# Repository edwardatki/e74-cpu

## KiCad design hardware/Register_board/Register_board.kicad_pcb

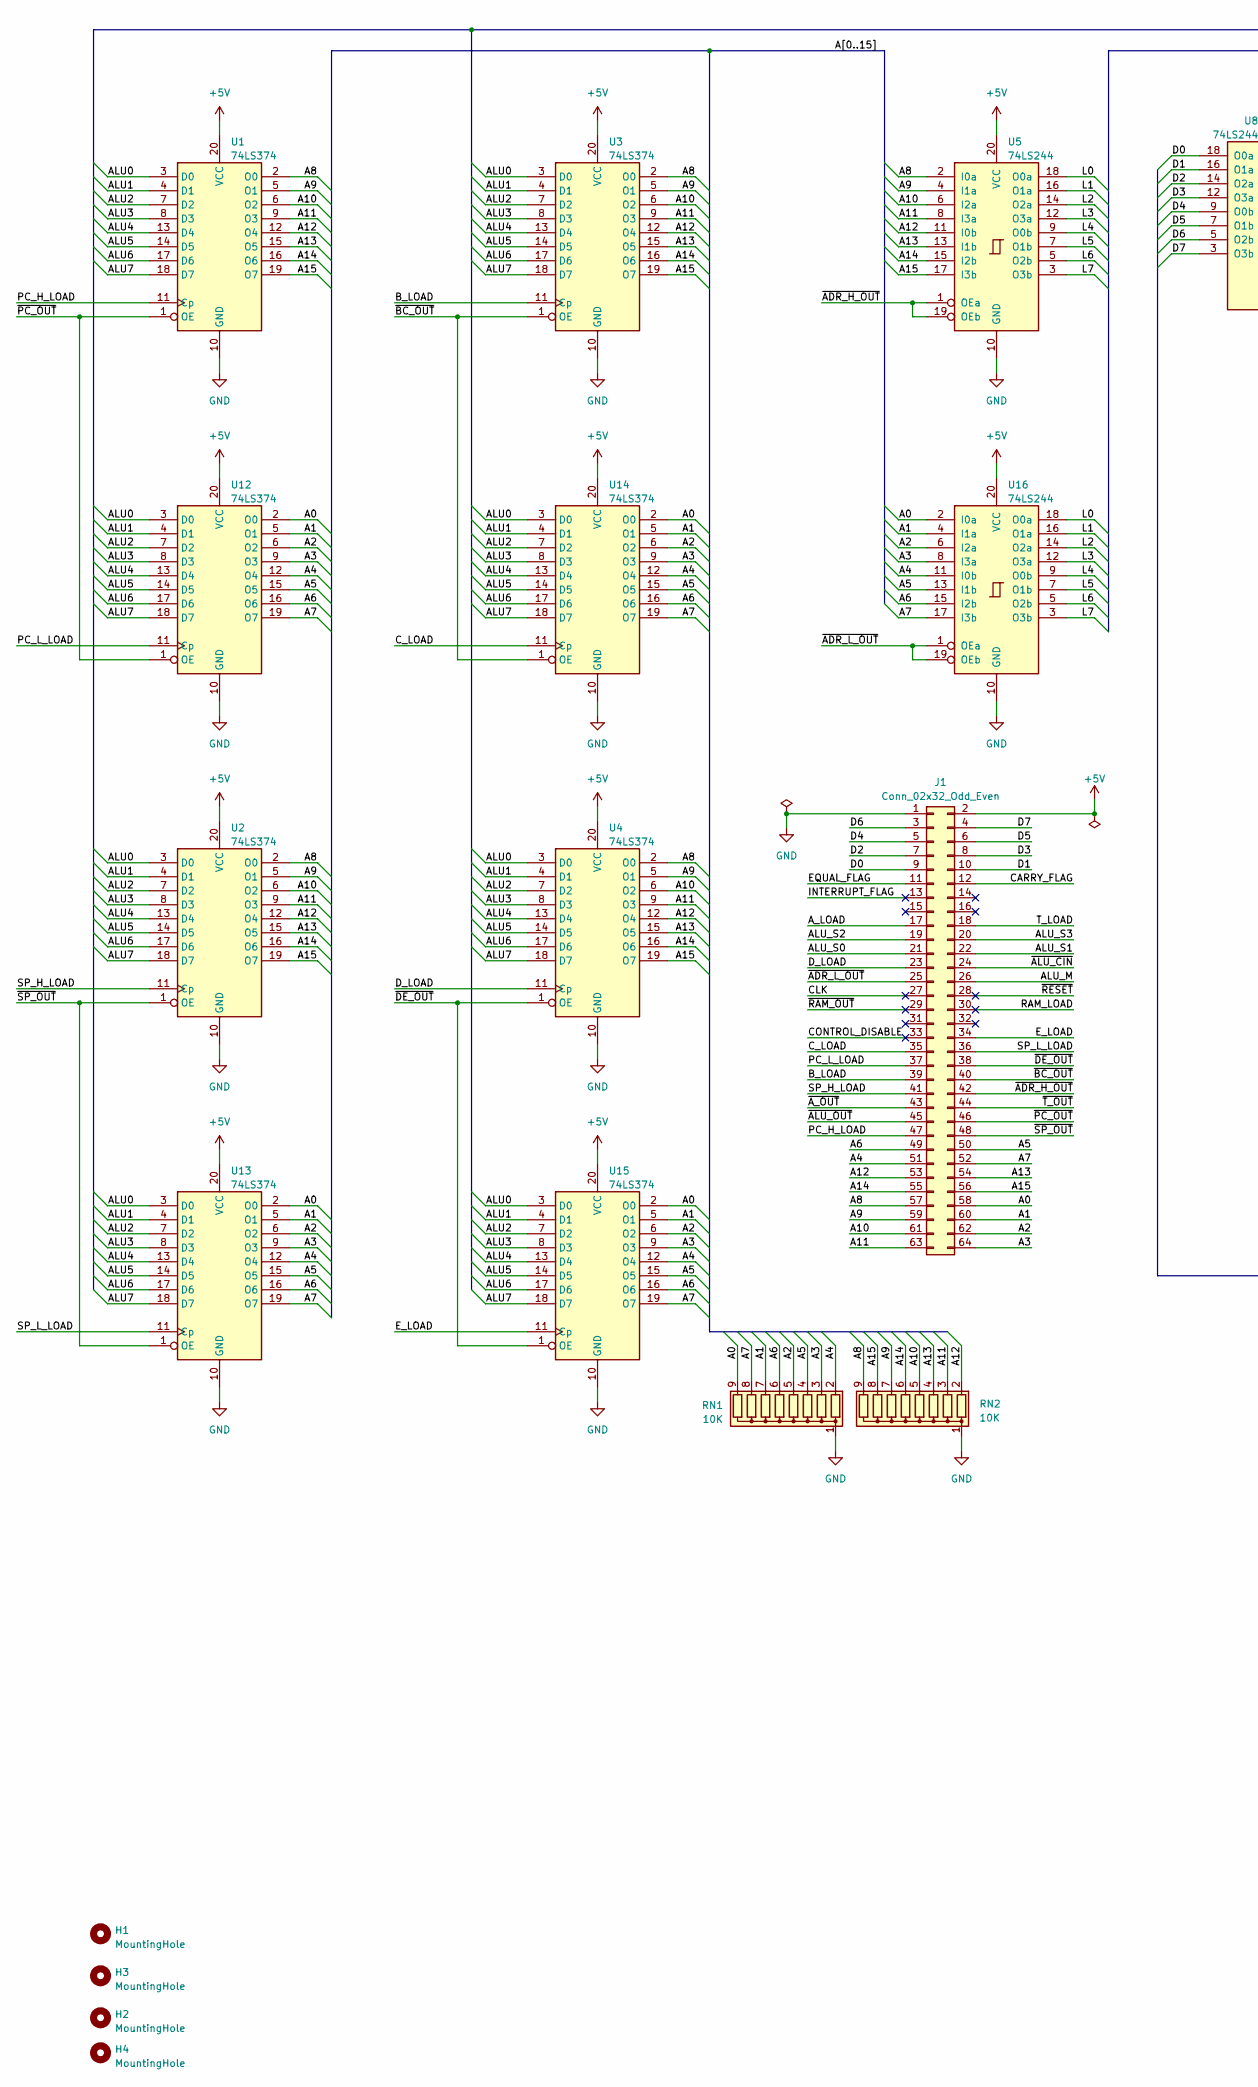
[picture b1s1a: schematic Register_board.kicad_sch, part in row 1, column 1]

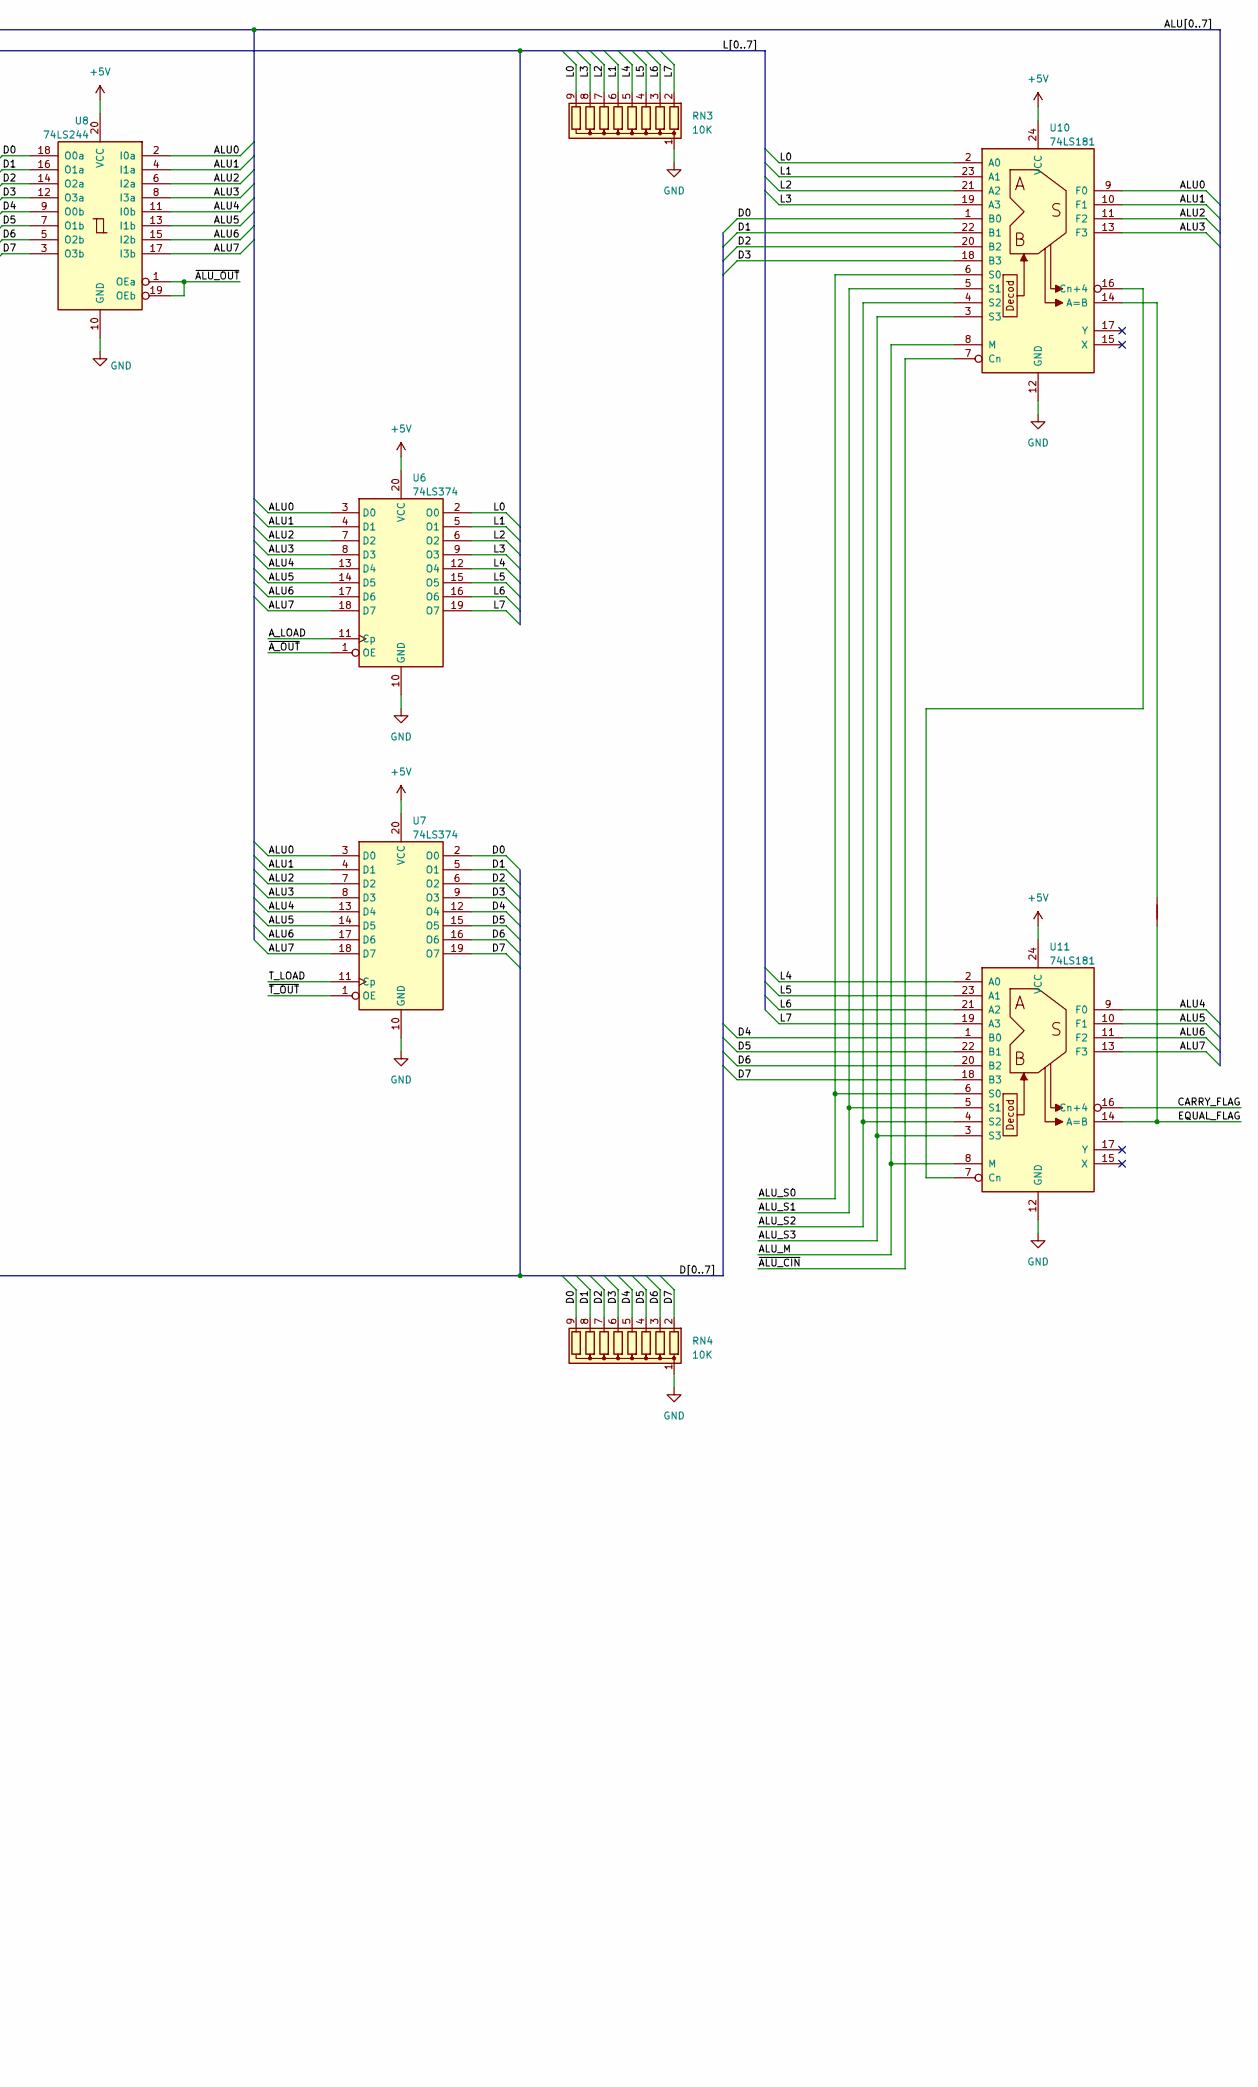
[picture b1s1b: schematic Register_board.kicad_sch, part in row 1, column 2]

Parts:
H1, H2, H3, H4: MountingHole; MountingHole_3.5mm
J1: Conn_02x32_Odd_Even; IDC-Header_2x32_P2.54mm_Vertical
NT1: NetTie_2; NetTie-2_SMD_Pad0.5mm
RN1, RN2, RN3, RN4: 10K; R_Array_SIP9
U1, U2, U3, U4, U6, U7, U12, U13, U14, U15: 74LS374; DIP-20_W7.62mm_Socket
U5, U8, U16: 74LS244; DIP-20_W7.62mm_Socket
U10, U11: 74LS181; DIP-24_W15.24mm_Socket

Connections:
+5V: J1.2, U1.20 (VCC), U2.20 (VCC), U3.20 (VCC), U4.20 (VCC), U5.20 (VCC), U6.20 (VCC), U7.20 (VCC), U8.20 (VCC), U10.24 (VCC), U11.24 (VCC), U12.20 (VCC), U13.20 (VCC), U14.20 (VCC), U15.20 (VCC), U16.20 (VCC); also elsewhere on the board
/A0: J1.58, RN1.9 (R8), U12.2 (O0), U13.2 (O0), U14.2 (O0), U15.2 (O0), U16.2 (I0a)
/A1: J1.60, RN1.7 (R6), U12.5 (O1), U13.5 (O1), U14.5 (O1), U15.5 (O1), U16.4 (I1a)
/A2: J1.62, RN1.5 (R4), U12.6 (O2), U13.6 (O2), U14.6 (O2), U15.6 (O2), U16.6 (I2a)
/A3: J1.64, RN1.3 (R2), U12.9 (O3), U13.9 (O3), U14.9 (O3), U15.9 (O3), U16.8 (I3a)
/A4: J1.51, RN1.2 (R1), U12.12 (O4), U13.12 (O4), U14.12 (O4), U15.12 (O4), U16.11 (I0b)
/A5: J1.50, RN1.4 (R3), U12.15 (O5), U13.15 (O5), U14.15 (O5), U15.15 (O5), U16.13 (I1b)
/A6: J1.49, RN1.6 (R5), U12.16 (O6), U13.16 (O6), U14.16 (O6), U15.16 (O6), U16.15 (I2b)
/A7: J1.52, RN1.8 (R7), U12.19 (O7), U13.19 (O7), U14.19 (O7), U15.19 (O7), U16.17 (I3b)
/A8: J1.57, RN2.9 (R8), U1.2 (O0), U2.2 (O0), U3.2 (O0), U4.2 (O0), U5.2 (I0a)
/A9: J1.59, RN2.7 (R6), U1.5 (O1), U2.5 (O1), U3.5 (O1), U4.5 (O1), U5.4 (I1a)
/A10: J1.61, RN2.5 (R4), U1.6 (O2), U2.6 (O2), U3.6 (O2), U4.6 (O2), U5.6 (I2a)
/A11: J1.63, RN2.3 (R2), U1.9 (O3), U2.9 (O3), U3.9 (O3), U4.9 (O3), U5.8 (I3a)
/A12: J1.53, RN2.2 (R1), U1.12 (O4), U2.12 (O4), U3.12 (O4), U4.12 (O4), U5.11 (I0b)
/A13: J1.54, RN2.4 (R3), U1.15 (O5), U2.15 (O5), U3.15 (O5), U4.15 (O5), U5.13 (I1b)
/A14: J1.55, RN2.6 (R5), U1.16 (O6), U2.16 (O6), U3.16 (O6), U4.16 (O6), U5.15 (I2b)
/A15: J1.56, RN2.8 (R7), U1.19 (O7), U2.19 (O7), U3.19 (O7), U4.19 (O7), U5.17 (I3b)
/ALU0: U1.3 (D0), U2.3 (D0), U3.3 (D0), U4.3 (D0), U6.3 (D0), U7.3 (D0), U8.2 (I0a), U10.9 (F0), U12.3 (D0), U13.3 (D0), U14.3 (D0), U15.3 (D0)
/ALU1: U1.4 (D1), U2.4 (D1), U3.4 (D1), U4.4 (D1), U6.4 (D1), U7.4 (D1), U8.4 (I1a), U10.10 (F1), U12.4 (D1), U13.4 (D1), U14.4 (D1), U15.4 (D1)
/ALU2: U1.7 (D2), U2.7 (D2), U3.7 (D2), U4.7 (D2), U6.7 (D2), U7.7 (D2), U8.6 (I2a), U10.11 (F2), U12.7 (D2), U13.7 (D2), U14.7 (D2), U15.7 (D2)
/ALU3: U1.8 (D3), U2.8 (D3), U3.8 (D3), U4.8 (D3), U6.8 (D3), U7.8 (D3), U8.8 (I3a), U10.13 (F3), U12.8 (D3), U13.8 (D3), U14.8 (D3), U15.8 (D3)
/ALU4: U1.13 (D4), U2.13 (D4), U3.13 (D4), U4.13 (D4), U6.13 (D4), U7.13 (D4), U8.11 (I0b), U11.9 (F0), U12.13 (D4), U13.13 (D4), U14.13 (D4), U15.13 (D4)
/ALU5: U1.14 (D5), U2.14 (D5), U3.14 (D5), U4.14 (D5), U6.14 (D5), U7.14 (D5), U8.13 (I1b), U11.10 (F1), U12.14 (D5), U13.14 (D5), U14.14 (D5), U15.14 (D5)
/ALU6: U1.17 (D6), U2.17 (D6), U3.17 (D6), U4.17 (D6), U6.17 (D6), U7.17 (D6), U8.15 (I2b), U11.11 (F2), U12.17 (D6), U13.17 (D6), U14.17 (D6), U15.17 (D6)
/ALU7: U1.18 (D7), U2.18 (D7), U3.18 (D7), U4.18 (D7), U6.18 (D7), U7.18 (D7), U8.17 (I3b), U11.13 (F3), U12.18 (D7), U13.18 (D7), U14.18 (D7), U15.18 (D7)
/ALU_M: J1.26, U10.8 (M), U11.8 (M)
/ALU_S0: J1.21, U10.6 (S0), U11.6 (S0)
/ALU_S1: J1.22, U10.5 (S1), U11.5 (S1)
/ALU_S2: J1.19, U10.4 (S2), U11.4 (S2)
/ALU_S3: J1.20, U10.3 (S3), U11.3 (S3)
/A_LOAD: J1.17, U6.11 (Cp)
/B_LOAD: J1.39, U3.11 (Cp)
/CARRY_FLAG_B: J1.16; also elsewhere on the board
/CLK: J1.27
/CONTROL_DISABLE: J1.33
/C_LOAD: J1.35, U14.11 (Cp)
/D0: J1.9, RN4.9 (R8), U7.2 (O0), U8.18 (O0a), U10.1 (B0)
/D1: J1.10, RN4.8 (R7), U7.5 (O1), U8.16 (O1a), U10.22 (B1)
/D2: J1.7, RN4.7 (R6), U7.6 (O2), U8.14 (O2a), U10.20 (B2)
/D3: J1.8, RN4.6 (R5), U7.9 (O3), U8.12 (O3a), U10.18 (B3)
/D4: J1.5, RN4.5 (R4), U7.12 (O4), U8.9 (O0b), U11.1 (B0)
/D5: J1.6, RN4.4 (R3), U7.15 (O5), U8.7 (O1b), U11.22 (B1)
/D6: J1.3, RN4.3 (R2), U7.16 (O6), U8.5 (O2b), U11.20 (B2)
/D7: J1.4, RN4.2 (R1), U7.19 (O7), U8.3 (O3b), U11.18 (B3)
/D_LOAD: J1.23, U4.11 (Cp)
/EQUAL_FLAG_B: J1.15; also elsewhere on the board
/E_LOAD: J1.34, U15.11 (Cp)
/FLAGS_A_UPDATE: J1.14; also elsewhere on the board
/FLAGS_B_UPDATE: J1.13; also elsewhere on the board
/L0: RN3.9 (R8), U5.18 (O0a), U6.2 (O0), U10.2 (A0), U16.18 (O0a)
/L1: RN3.6 (R5), U5.16 (O1a), U6.5 (O1), U10.23 (A1), U16.16 (O1a)
/L2: RN3.7 (R6), U5.14 (O2a), U6.6 (O2), U10.21 (A2), U16.14 (O2a)
/L3: RN3.8 (R7), U5.12 (O3a), U6.9 (O3), U10.19 (A3), U16.12 (O3a)
/L4: RN3.5 (R4), U5.9 (O0b), U6.12 (O4), U11.2 (A0), U16.9 (O0b)
/L5: RN3.4 (R3), U5.7 (O1b), U6.15 (O5), U11.23 (A1), U16.7 (O1b)
/L6: RN3.3 (R2), U5.5 (O2b), U6.16 (O6), U11.21 (A2), U16.5 (O2b)
/L7: RN3.2 (R1), U5.3 (O3b), U6.19 (O7), U11.19 (A3), U16.3 (O3b)
/PC_H_LOAD: J1.47, U1.11 (Cp)
/PC_L_LOAD: J1.37, U12.11 (Cp)
/RAM_LOAD: J1.30
/SP_H_LOAD: J1.41, U2.11 (Cp)
/SP_L_LOAD: J1.36, U13.11 (Cp)
/T_LOAD: J1.18, U7.11 (Cp)
/~ADR_H_OUT: J1.42, U5.1 (OEa), U5.19 (OEb)
/~ADR_L_OUT: J1.25, U16.1 (OEa), U16.19 (OEb)
/~ALU_CIN: J1.24, U10.7 (Cn)
/~ALU_OUT: J1.45, U8.1 (OEa), U8.19 (OEb)
/~A_OUT: J1.43, U6.1 (OE)
/~BC_OUT: J1.40, U3.1 (OE), U14.1 (OE)
/~DE_OUT: J1.38, U4.1 (OE), U15.1 (OE)
/~PC_OUT: J1.46, U1.1 (OE), U12.1 (OE)
/~RAM_OUT: J1.29
/~RESET: J1.28
/~SP_OUT: J1.48, U2.1 (OE), U13.1 (OE)
/~T_OUT: J1.44, U7.1 (OE)
GND: J1.1, RN1.1 (common), RN2.1 (common), RN3.1 (common), RN4.1 (common), U1.10 (GND), U2.10 (GND), U3.10 (GND), U4.10 (GND), U5.10 (GND), U6.10 (GND), U7.10 (GND), U8.10 (GND), U10.12 (GND), U11.12 (GND), U12.10 (GND), U13.10 (GND), U14.10 (GND), U15.10 (GND), U16.10 (GND); also elsewhere on the board
unnamed: NT1.1, U10.14 (A=B)
unnamed: U10.16 (Cn+4), U11.7 (Cn)

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
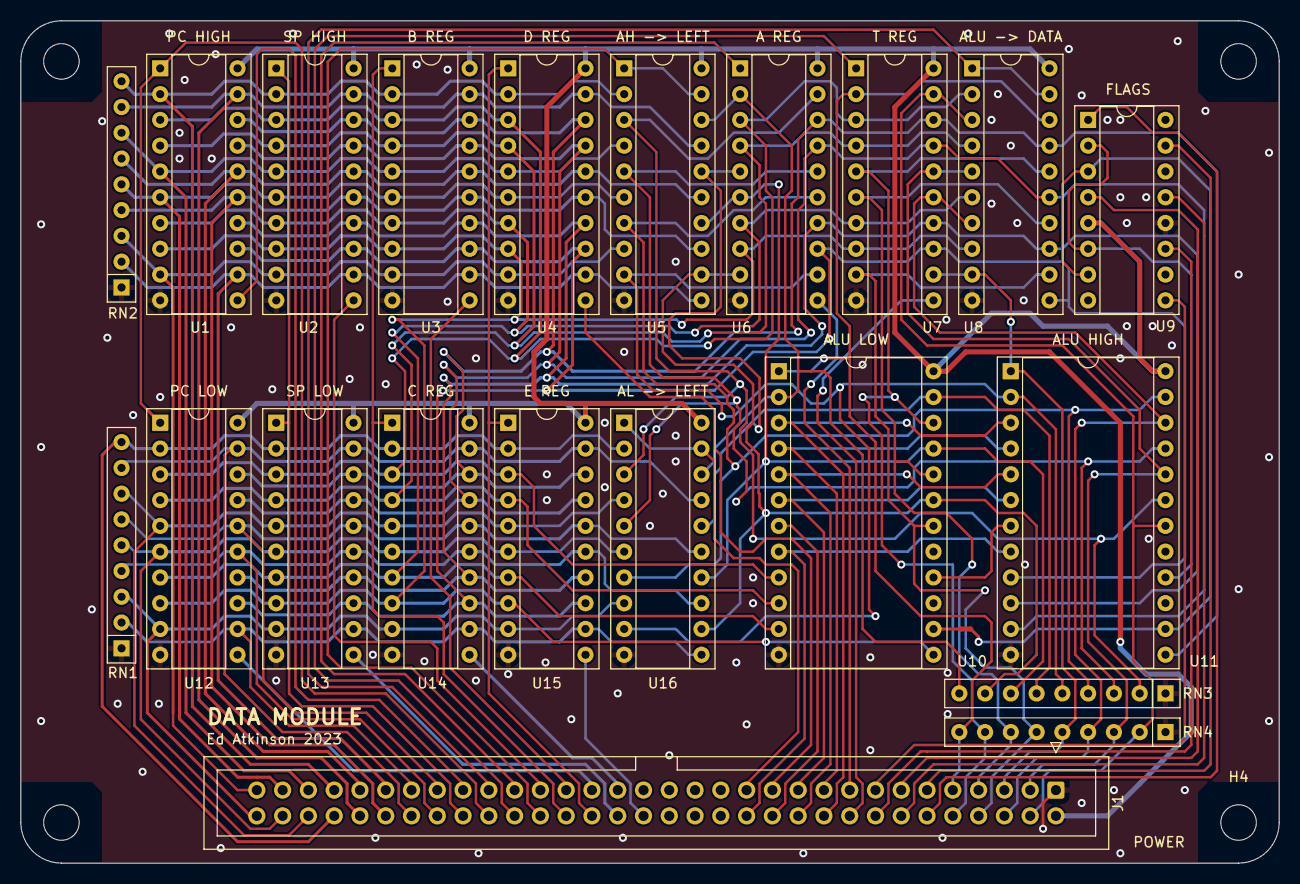
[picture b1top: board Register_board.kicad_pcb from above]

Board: 2 copper layers, 124.0 x 83.0 mm, 26 parts (0 on the bottom side), 77 nets.

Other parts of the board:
U9: 74LS75; DIP-16_W7.62mm_Socket

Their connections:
+5V: U9.5 (VCC); also elsewhere on the board
/CARRY_FLAG_B: U9.11 (~Q2); also elsewhere on the board
/EQUAL_FLAG_B: U9.9 (Q3); also elsewhere on the board
/FLAGS_A_UPDATE: U9.13 (E01); also elsewhere on the board
/FLAGS_B_UPDATE: U9.4 (E23); also elsewhere on the board
GND: U9.12 (GND); also elsewhere on the board

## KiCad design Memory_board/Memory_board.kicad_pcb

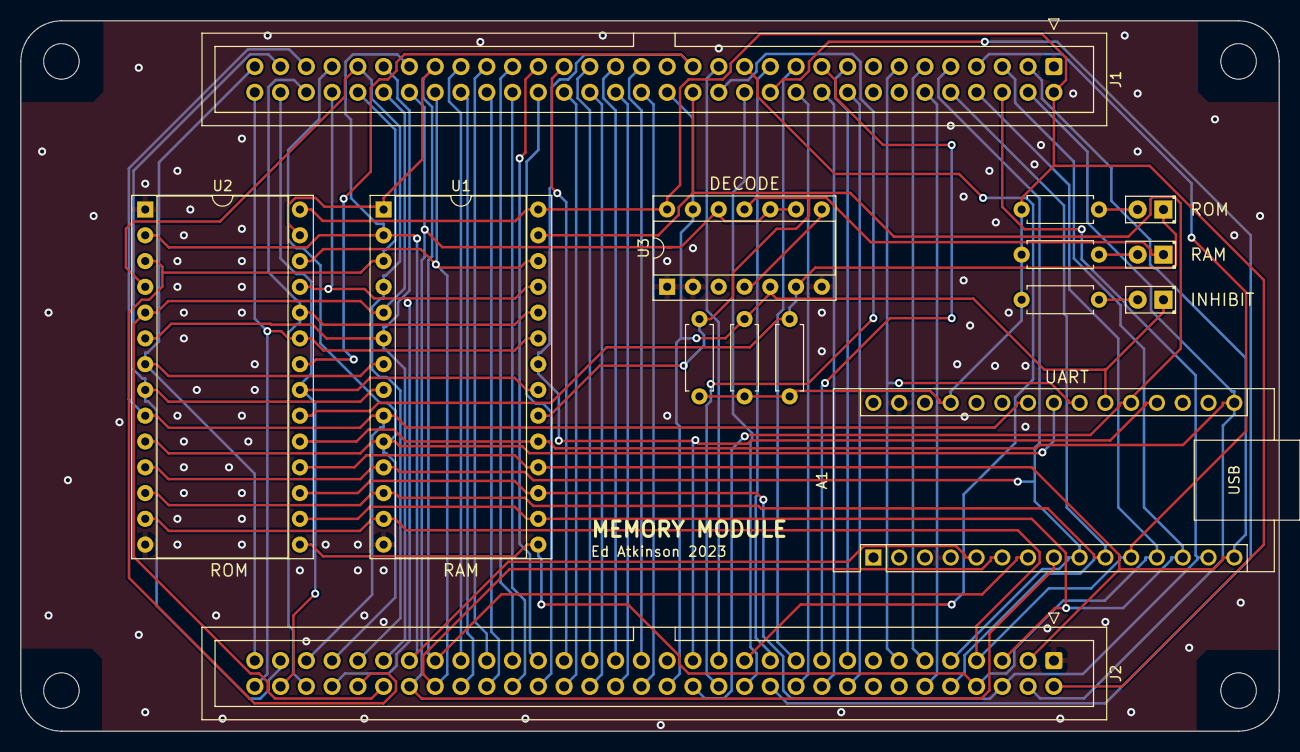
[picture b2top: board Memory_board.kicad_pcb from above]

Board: 2 copper layers, 124.0 x 70.0 mm, 19 parts (0 on the bottom side), 66 nets.

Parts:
A1: Arduino_Nano_v3.x; Arduino_Nano
D1, D2, D3: LED; LED_D2.0mm_W4.8mm_H2.5mm_FlatTop
H1, H2, H3, H4: MountingHole; MountingHole_3.5mm
J1, J2: Conn_02x32_Odd_Even; IDC-Header_2x32_P2.54mm_Vertical
R1, R5, R6: 1K; R_Axial_DIN0207_L6.3mm_D2.5mm_P7.62mm_Horizontal
R2, R3, R4: 330R; R_Axial_DIN0207_L6.3mm_D2.5mm_P7.62mm_Horizontal
U1: CY62256-70PC; DIP-28_W15.24mm_Socket
U2: 27C512; DIP-28_W15.24mm_Socket
U3: 74LS00; DIP-14_W7.62mm_Socket

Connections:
+5V: A1.27 (+5V), J1.2, J2.2, R1.2, R2.2, R3.2, R4.2, R5.1, R6.1, U1.28 (VCC), U2.28 (VCC), U3.14 (VCC)
/A0: A1.23 (A4), J1.57, J2.57, U1.10 (A0), U2.10 (A0)
/A1: A1.24 (A5), J1.59, J2.59, U1.9 (A1), U2.9 (A1)
/A2: J1.61, J2.61, U1.8 (A2), U2.8 (A2)
/A3: J1.63, J2.63, U1.7 (A3), U2.7 (A3)
/A4: J1.53, J2.53, U1.6 (A4), U2.6 (A4)
/A5: J1.54, J2.54, U1.5 (A5), U2.5 (A5)
/A6: J1.55, J2.55, U1.4 (A6), U2.4 (A6)
/A7: J1.56, J2.56, U1.3 (A7), U2.3 (A7)
/A8: J1.58, J2.58, U1.25 (A8), U2.25 (A8)
/A9: J1.60, J2.60, U1.24 (A9), U2.24 (A9)
/A10: J1.62, J2.62, U1.21 (A10), U2.21 (A10)
/A11: J1.64, J2.64, U1.23 (A11), U2.23 (A11)
/A12: A1.5 (D2), J1.51, J2.51, U1.2 (A12), U2.2 (A12)
/A13: A1.6 (D3), J1.50, J2.50, U1.26 (A13), U2.26 (A13)
/A14: A1.7 (D4), J1.49, J2.49, U1.1 (A14), U2.27 (A14)
/A15: A1.8 (D5), J1.52, J2.52, U3.9, U3.10, U3.12
/ALU_M: J1.26, J2.26
/ALU_S0: J1.21, J2.21
/ALU_S1: J1.22, J2.22
/ALU_S2: J1.19, J2.19
/ALU_S3: J1.20, J2.20
/A_LOAD: J1.17, J2.17
/B_LOAD: J1.39, J2.39
/CARRY_FLAG: J1.12, J2.12
/CLK: J1.27, J2.27
/CONTROL_DISABLE: J1.33, J2.33
/C_LOAD: J1.35, J2.35
/D0: A1.9 (D6), J1.9, J2.9, U1.11 (Q0), U2.11 (D0)
/D1: A1.10 (D7), J1.10, J2.10, U1.12 (Q1), U2.12 (D1)
/D2: A1.11 (D8), J1.7, J2.7, U1.13 (Q2), U2.13 (D2)
/D3: A1.12 (D9), J1.8, J2.8, U1.15 (Q3), U2.15 (D3)
/D4: A1.13 (D10), J1.5, J2.5, U1.16 (Q4), U2.16 (D4)
/D5: A1.14 (D11), J1.6, J2.6, U1.17 (Q5), U2.17 (D5)
/D6: A1.15 (D12), J1.3, J2.3, U1.18 (Q6), U2.18 (D6)
/D7: A1.16 (D13), J1.4, J2.4, U1.19 (Q7), U2.19 (D7)
/D_LOAD: J1.23, J2.23
/EQUAL_FLAG: J1.11, J2.11
/E_LOAD: J1.34, J2.34
/PC_H_LOAD: J1.47, J2.47
/PC_L_LOAD: J1.37, J2.37
/SP_H_LOAD: J1.41, J2.41
/SP_L_LOAD: J1.36, J2.36
/T_LOAD: J1.18, J2.18
/~ADR_H_OUT: J1.42, J2.42
/~ADR_L_OUT: J1.25, J2.25
/~ALU_CIN: J1.24, J2.24
/~ALU_OUT: J1.45, J2.45
/~A_OUT: J1.43, J2.43
/~BC_OUT: J1.40, J2.40
/~DE_OUT: J1.38, J2.38
/~INTERRUPT_FLAG: A1.22 (A3), J1.13, J2.13
/~MEM_INHIBIT: A1.21 (A2), D3.1 (K), J1.32, J2.32, R1.1, U3.5, U3.13
/~MEM_LOAD: A1.20 (A1), J1.30, J2.30, U1.27 (~WE)
/~MEM_OUT: A1.19 (A0), J1.29, J2.29, U1.22 (~OE), U2.22 (~OE)
/~PC_OUT: J1.46, J2.46
/~RAM_CE: D1.1 (K), R5.2, U1.20 (~CS), U3.11
/~RESET: J1.28, J2.28
/~ROM_CE: D2.1 (K), R6.2, U2.20 (~CE), U3.6
/~SP_OUT: J1.48, J2.48
/~T_OUT: J1.44, J2.44
GND: A1.4 (GND), A1.29 (GND), J1.1, J2.1, U1.14 (GND), U2.1 (A15), U2.14 (GND), U3.1, U3.2, U3.7 (GND)
unnamed: D1.2 (A), R2.1
unnamed: D2.2 (A), R3.1
unnamed: D3.2 (A), R4.1
unnamed: U3.4, U3.8

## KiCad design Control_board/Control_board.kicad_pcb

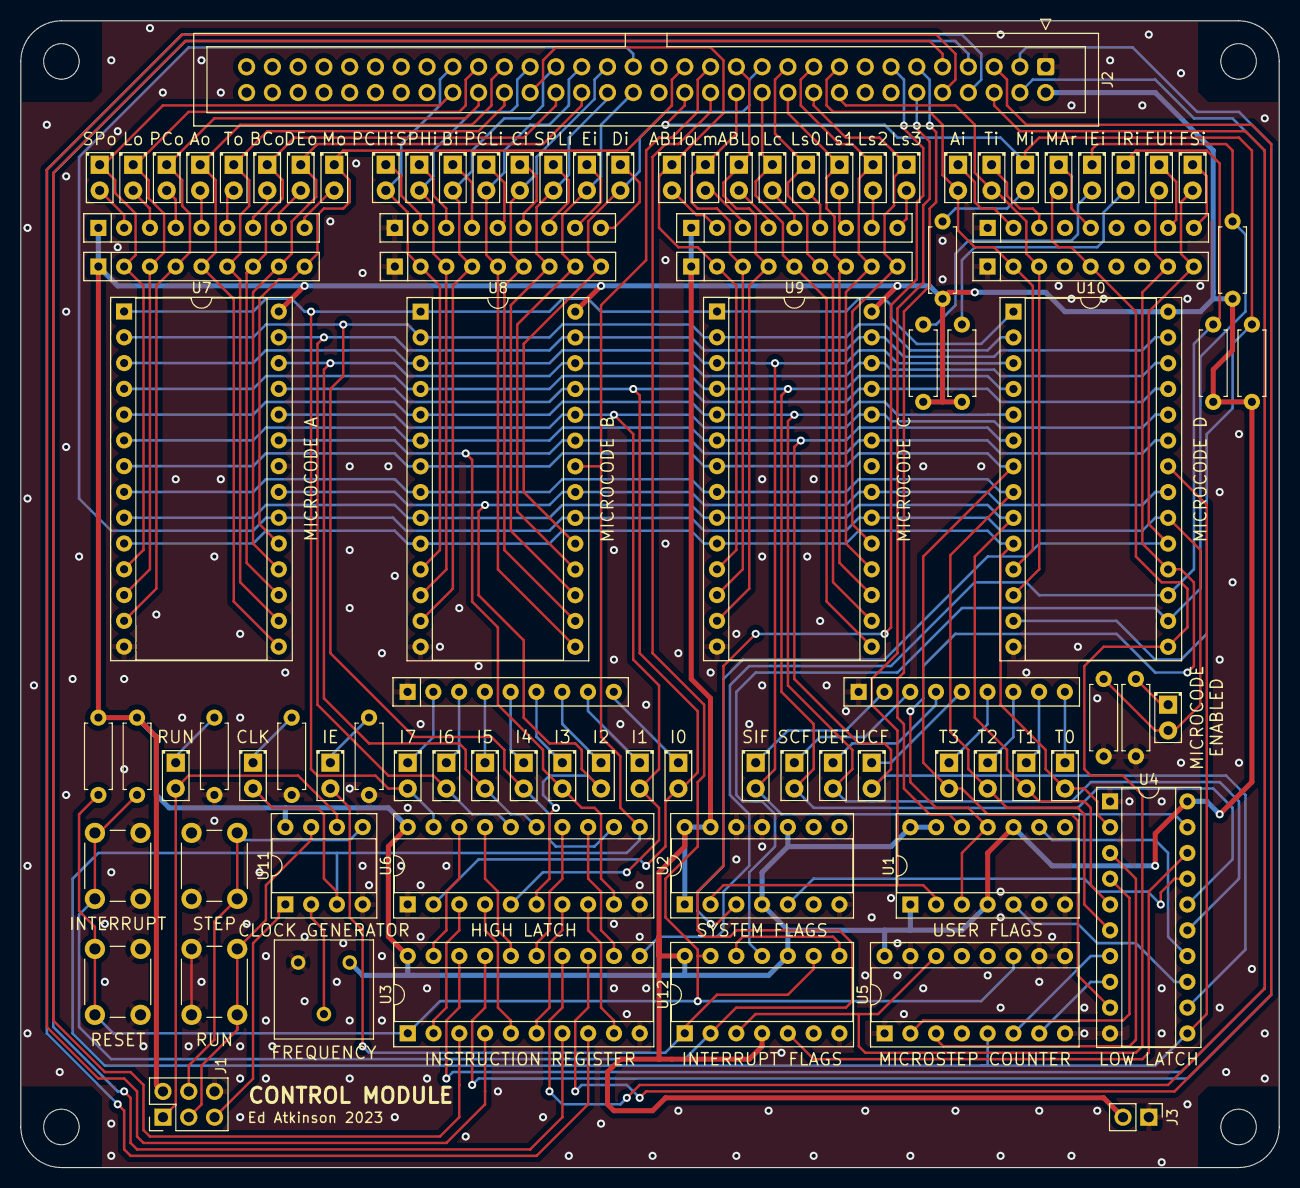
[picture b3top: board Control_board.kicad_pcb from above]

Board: 2 copper layers, 124.0 x 113.0 mm, 99 parts (0 on the bottom side), 139 nets.

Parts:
D1, D2, D3, D4, D5, D6, D7, D8, D9, D10, D11, D12, D13, D14, D15, D16, D17, D18, D19, D20, D21, D22, D23, D24, D25, D26, D27, D28, D29, D30, D31, D32, D33, D34, D35, D36, D37, D38, D39, D40, D41, D42, D43, D44, D45, D46, D47, D48, D49, D50, D51, D52: LED; LED_D2.0mm_W4.8mm_H2.5mm_FlatTop
H1, H2, H3, H4: MountingHole; MountingHole_3.5mm
J1: ICSP; PinHeader_2x03_P2.54mm_Vertical
J2: Conn_02x32_Odd_Even; IDC-Header_2x32_P2.54mm_Vertical
J3: Conn_01x02; PinHeader_1x02_P2.54mm_Vertical
R1, R5, R6, R10, R11, R13: 1K; R_Axial_DIN0207_L6.3mm_D2.5mm_P7.62mm_Horizontal
R2, R3, R4, R7, R8, R9, R12: 330R; R_Axial_DIN0207_L6.3mm_D2.5mm_P7.62mm_Horizontal
RN1, RN2, RN3, RN4: 1K; R_Array_SIP9
RN5, RN6, RN7, RN8, RN9, RN10: 330R; R_Array_SIP9
RV1: R_Potentiometer; Potentiometer_Bourns_3386F_Vertical
SW1, SW2, SW3, SW4: SW_Push; SW_PUSH_6mm
U1, U2, U12: 74LS74; DIP-14_W7.62mm_Socket
U3: 74LS273; DIP-20_W7.62mm_Socket
U4, U6: 74LS373; DIP-20_W7.62mm_Socket
U5: 74LS192; DIP-16_W7.62mm_Socket
U7, U8, U9, U10: 27C512; DIP-28_W15.24mm_Socket
U11: ATtiny85-20P; DIP-8_W7.62mm_Socket

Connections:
+5V: J1.2, J2.2, J3.2, R1.1, R5.1, R6.1, R7.2, R8.2, R9.2, R10.1, R13.1, RN3.1 (common), RN4.1 (common), RN8.1 (common), RN10.1 (common), RV1.3, U1.1 (~R), U1.4 (~S), U1.10 (~S), U1.13 (~R), U1.14 (VCC), U2.1 (~R), U2.4 (~S), U2.10 (~S), U2.13 (~R), U2.14 (VCC), U3.20 (VCC), U4.20 (VCC), U5.16 (VCC), U6.20 (VCC), U7.28 (VCC), U8.28 (VCC), U9.28 (VCC), U10.28 (VCC), U11.8 (VCC), U12.4 (~S), U12.10 (~S), U12.14 (VCC)
/ALU_M: D45.1 (K), J2.26, RN4.3 (R2), U9.12 (D1)
/ALU_S0: D48.1 (K), J2.21, RN4.6 (R5), U9.16 (D4)
/ALU_S1: D49.1 (K), J2.22, RN4.7 (R6), U9.17 (D5)
/ALU_S2: D50.1 (K), J2.19, RN4.8 (R7), U9.18 (D6)
/ALU_S3: D51.1 (K), J2.20, RN4.9 (R8), U9.19 (D7)
/A_LOAD: D23.2 (A), J2.17, RN1.2 (R1), U10.11 (D0)
/B_LOAD: D38.2 (A), J2.39, RN2.4 (R3), U8.13 (D2)
/CARRY_FLAG: J2.12, U1.2 (D), U2.2 (D)
/CLK: D2.2 (A), J2.27, U4.11 (LE), U5.5 (UP), U6.11 (LE), U8.22 (~OE), U10.22 (~OE), U11.3 (XTAL2/PB4)
/CONTROL_DISABLE: D52.2 (A), J2.33, R11.1, U7.20 (~CE), U8.20 (~CE), U9.20 (~CE), U10.20 (~CE)
/COUNTER_RESET: D25.2 (A), RN1.5 (R4), U5.14 (CLR), U10.15 (D3), U12.3 (C)
/C_LOAD: D40.2 (A), J2.35, RN2.6 (R5), U8.16 (D4)
/D0: J2.9, U3.3 (D0)
/D1: J2.10, U3.4 (D1)
/D2: J2.7, U3.7 (D2)
/D3: J2.8, U3.8 (D3)
/D4: J2.5, U3.13 (D4)
/D5: J2.6, U3.14 (D5)
/D6: J2.3, U3.17 (D6)
/D7: J2.4, U3.18 (D7)
/D_LOAD: D43.2 (A), J2.23, RN2.9 (R8), U8.19 (D7)
/EQUAL_FLAG: J2.11, U1.12 (D)
/E_LOAD: D42.2 (A), J2.34, RN2.8 (R7), U8.18 (D6)
/FLAGS_A_UPDATE: D26.2 (A), RN1.8 (R7), U1.3 (C), U1.11 (C), U10.18 (D6)
/FLAGS_B_UPDATE: D27.2 (A), RN1.9 (R8), U2.3 (C), U10.19 (D7)
/INT_EN_TOGGLE: D21.1 (K), R5.2, U10.16 (D4), U12.11 (C)
/IR_LOAD: D20.1 (K), R1.2, U3.11 (Cp), U10.17 (D5)
/MA0: D3.2 (A), U4.2 (O0), U7.10 (A0), U8.10 (A0), U9.10 (A0), U10.10 (A0)
/MA1: D4.2 (A), U4.5 (O1), U7.9 (A1), U8.9 (A1), U9.9 (A1), U10.9 (A1)
/MA2: D5.2 (A), U4.6 (O2), U7.8 (A2), U8.8 (A2), U9.8 (A2), U10.8 (A2)
/MA3: D7.2 (A), U4.9 (O3), U7.7 (A3), U8.7 (A3), U9.7 (A3), U10.7 (A3)
/MA4: D8.2 (A), U4.12 (O4), U7.6 (A4), U8.6 (A4), U9.6 (A4), U10.6 (A4)
/MA5: D9.2 (A), U4.15 (O5), U7.5 (A5), U8.5 (A5), U9.5 (A5), U10.5 (A5)
/MA6: D10.2 (A), U4.16 (O6), U7.4 (A6), U8.4 (A6), U9.4 (A6), U10.4 (A6)
/MA7: D11.2 (A), U4.19 (O7), U7.3 (A7), U8.3 (A7), U9.3 (A7), U10.3 (A7)
/MA8: D12.2 (A), U6.2 (O0), U7.25 (A8), U8.25 (A8), U9.25 (A8), U10.25 (A8)
/MA9: D13.2 (A), U6.5 (O1), U7.24 (A9), U8.24 (A9), U9.24 (A9), U10.24 (A9)
/MA10: D14.2 (A), U6.6 (O2), U7.21 (A10), U8.21 (A10), U9.21 (A10), U10.21 (A10)
/MA11: D15.2 (A), U6.9 (O3), U7.23 (A11), U8.23 (A11), U9.23 (A11), U10.23 (A11)
/MA12: D16.2 (A), U6.12 (O4), U7.2 (A12), U8.2 (A12), U9.2 (A12), U10.2 (A12)
/MA13: D17.2 (A), U6.15 (O5), U7.26 (A13), U8.26 (A13), U9.26 (A13), U10.26 (A13)
/MA14: D18.2 (A), U6.16 (O6), U7.27 (A14), U8.27 (A14), U9.27 (A14), U10.27 (A14)
/MA15: D19.2 (A), U6.19 (O7), U7.1 (A15), U8.1 (A15), U9.1 (A15), U10.1 (A15)
/PC_H_LOAD: D36.2 (A), J2.47, RN2.2 (R1), U8.11 (D0)
/PC_L_LOAD: D39.2 (A), J2.37, RN2.5 (R4), U8.15 (D3)
/SP_H_LOAD: D37.2 (A), J2.41, RN2.3 (R2), U8.12 (D1)
/SP_L_LOAD: D41.2 (A), J2.36, RN2.7 (R6), U8.17 (D5)
/T_LOAD: D24.2 (A), J2.18, RN1.3 (R2), U10.12 (D1)
/~ADR_H_OUT: D44.1 (K), J2.42, RN4.2 (R1), U9.11 (D0)
/~ADR_L_OUT: D46.1 (K), J2.25, RN4.4 (R3), U9.13 (D2)
/~ALU_CIN: D47.1 (K), J2.24, RN4.5 (R4), U9.15 (D3)
/~ALU_OUT: D29.1 (K), J2.45, RN3.3 (R2), U7.12 (D1)
/~A_OUT: D31.1 (K), J2.43, RN3.5 (R4), U7.15 (D3)
/~BC_OUT: D33.1 (K), J2.40, RN3.7 (R6), U7.17 (D5)
/~DE_OUT: D34.1 (K), J2.38, RN3.8 (R7), U7.18 (D6)
/~INTERRUPT_FLAG: J2.13, R13.2, SW4.1, U12.2 (D)
/~PC_OUT: D30.1 (K), J2.46, RN3.4 (R3), U7.13 (D2)
/~RAM_LOAD: D22.1 (K), J2.30, R6.2, U10.13 (D2)
/~RAM_OUT: D35.1 (K), J2.29, RN3.9 (R8), U7.19 (D7)
/~RESET: J2.28, R10.2, SW3.1, U3.1 (~Mr), U5.11 (~LOAD), U12.13 (~R)
/~SP_OUT: D28.1 (K), J2.48, RN3.2 (R1), U7.11 (D0)
/~T_OUT: D32.1 (K), J2.44, RN3.6 (R5), U7.16 (D4)
GND: J1.6, J2.1, J3.1, R2.2, R3.2, R4.2, R11.2, R12.2, RN1.1 (common), RN2.1 (common), RN5.1 (common), RN6.1 (common), RN7.1 (common), RN9.1 (common), RV1.1, SW1.2, SW2.2, SW3.2, SW4.2, U1.7 (GND), U2.7 (GND), U2.11 (C), U2.12 (D), U3.10 (GND), U4.1 (OE), U4.10 (GND), U5.1 (B), U5.4 (DOWN), U5.8 (GND), U5.9 (D), U5.10 (C), U5.15 (A), U6.1 (OE), U6.10 (GND), U7.14 (GND), U7.22 (~OE), U8.14 (GND), U9.14 (GND), U9.22 (~OE), U10.14 (GND), U11.4 (GND), U12.7 (GND)
unnamed: D1.2 (A), J1.1, U11.6 (PB1)
unnamed: D1.1 (K), R2.1
unnamed: D2.1 (K), R3.1
unnamed: D3.1 (K), RN5.9 (R8)
unnamed: D4.1 (K), RN5.8 (R7)
unnamed: D5.1 (K), RN5.7 (R6)
unnamed: D6.2 (A), U12.1 (~R), U12.9 (Q)
unnamed: D6.1 (K), R4.1
unnamed: D7.1 (K), RN5.6 (R5)
unnamed: D8.1 (K), RN5.5 (R4)
unnamed: D9.1 (K), RN5.4 (R3)
unnamed: D10.1 (K), RN5.3 (R2)
unnamed: D11.1 (K), RN5.2 (R1)
unnamed: D12.1 (K), RN6.9 (R8)
unnamed: D13.1 (K), RN6.8 (R7)
unnamed: D14.1 (K), RN6.7 (R6)
unnamed: D15.1 (K), RN6.6 (R5)
unnamed: D16.1 (K), RN6.5 (R4)
unnamed: D17.1 (K), RN6.4 (R3)
unnamed: D18.1 (K), RN6.3 (R2)
unnamed: D19.1 (K), RN6.2 (R1)
unnamed: D20.2 (A), R7.1
unnamed: D21.2 (A), R8.1
unnamed: D22.2 (A), R9.1
unnamed: D23.1 (K), RN7.2 (R1)
unnamed: D24.1 (K), RN7.3 (R2)
unnamed: D25.1 (K), RN7.5 (R4)
unnamed: D26.1 (K), RN7.8 (R7)
unnamed: D27.1 (K), RN7.9 (R8)
unnamed: D28.2 (A), RN8.2 (R1)
unnamed: D29.2 (A), RN8.3 (R2)
unnamed: D30.2 (A), RN8.4 (R3)
unnamed: D31.2 (A), RN8.5 (R4)
unnamed: D32.2 (A), RN8.6 (R5)
unnamed: D33.2 (A), RN8.7 (R6)
unnamed: D34.2 (A), RN8.8 (R7)
unnamed: D35.2 (A), RN8.9 (R8)
unnamed: D36.1 (K), RN9.2 (R1)
unnamed: D37.1 (K), RN9.3 (R2)
unnamed: D38.1 (K), RN9.4 (R3)
unnamed: D39.1 (K), RN9.5 (R4)
unnamed: D40.1 (K), RN9.6 (R5)
unnamed: D41.1 (K), RN9.7 (R6)
unnamed: D42.1 (K), RN9.8 (R7)
unnamed: D43.1 (K), RN9.9 (R8)
unnamed: D44.2 (A), RN10.2 (R1)
unnamed: D45.2 (A), RN10.3 (R2)
unnamed: D46.2 (A), RN10.4 (R3)
unnamed: D47.2 (A), RN10.5 (R4)
unnamed: D48.2 (A), RN10.6 (R5)
unnamed: D49.2 (A), RN10.7 (R6)
unnamed: D50.2 (A), RN10.8 (R7)
unnamed: D51.2 (A), RN10.9 (R8)
unnamed: D52.1 (K), R12.1
unnamed: J1.3, SW1.1, U11.7 (PB2)
unnamed: J1.4, SW2.1, U11.5 (AREF/PB0)
unnamed: J1.5, U11.1 (~RESET/PB5)
unnamed: U1.5 (Q), U4.13 (D4)
unnamed: U1.9 (Q), U4.14 (D5)
unnamed: U2.5 (Q), U4.17 (D6)
unnamed: U3.2 (Q0), U6.3 (D0)
unnamed: U3.5 (Q1), U6.4 (D1)
unnamed: U3.6 (Q2), U6.7 (D2)
unnamed: U3.9 (Q3), U6.8 (D3)
unnamed: U3.12 (Q4), U6.13 (D4)
unnamed: U3.15 (Q5), U6.14 (D5)
unnamed: U3.16 (Q6), U6.17 (D6)
unnamed: U3.19 (Q7), U6.18 (D7)
unnamed: U4.3 (D0), U5.3 (QA)
unnamed: U4.4 (D1), U5.2 (QB)
unnamed: U4.7 (D2), U5.6 (QC)
unnamed: U4.8 (D3), U5.7 (QD)
unnamed: RV1.2, U11.2 (XTAL1/PB3)
unnamed: U4.18 (D7), U12.5 (Q)
unnamed: U12.8 (~Q), U12.12 (D)
